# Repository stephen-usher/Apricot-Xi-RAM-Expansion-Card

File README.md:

# Apricot-Xi-RAM-Expansion-Card
ACT Apricot Xi/PC RAM expansion card.

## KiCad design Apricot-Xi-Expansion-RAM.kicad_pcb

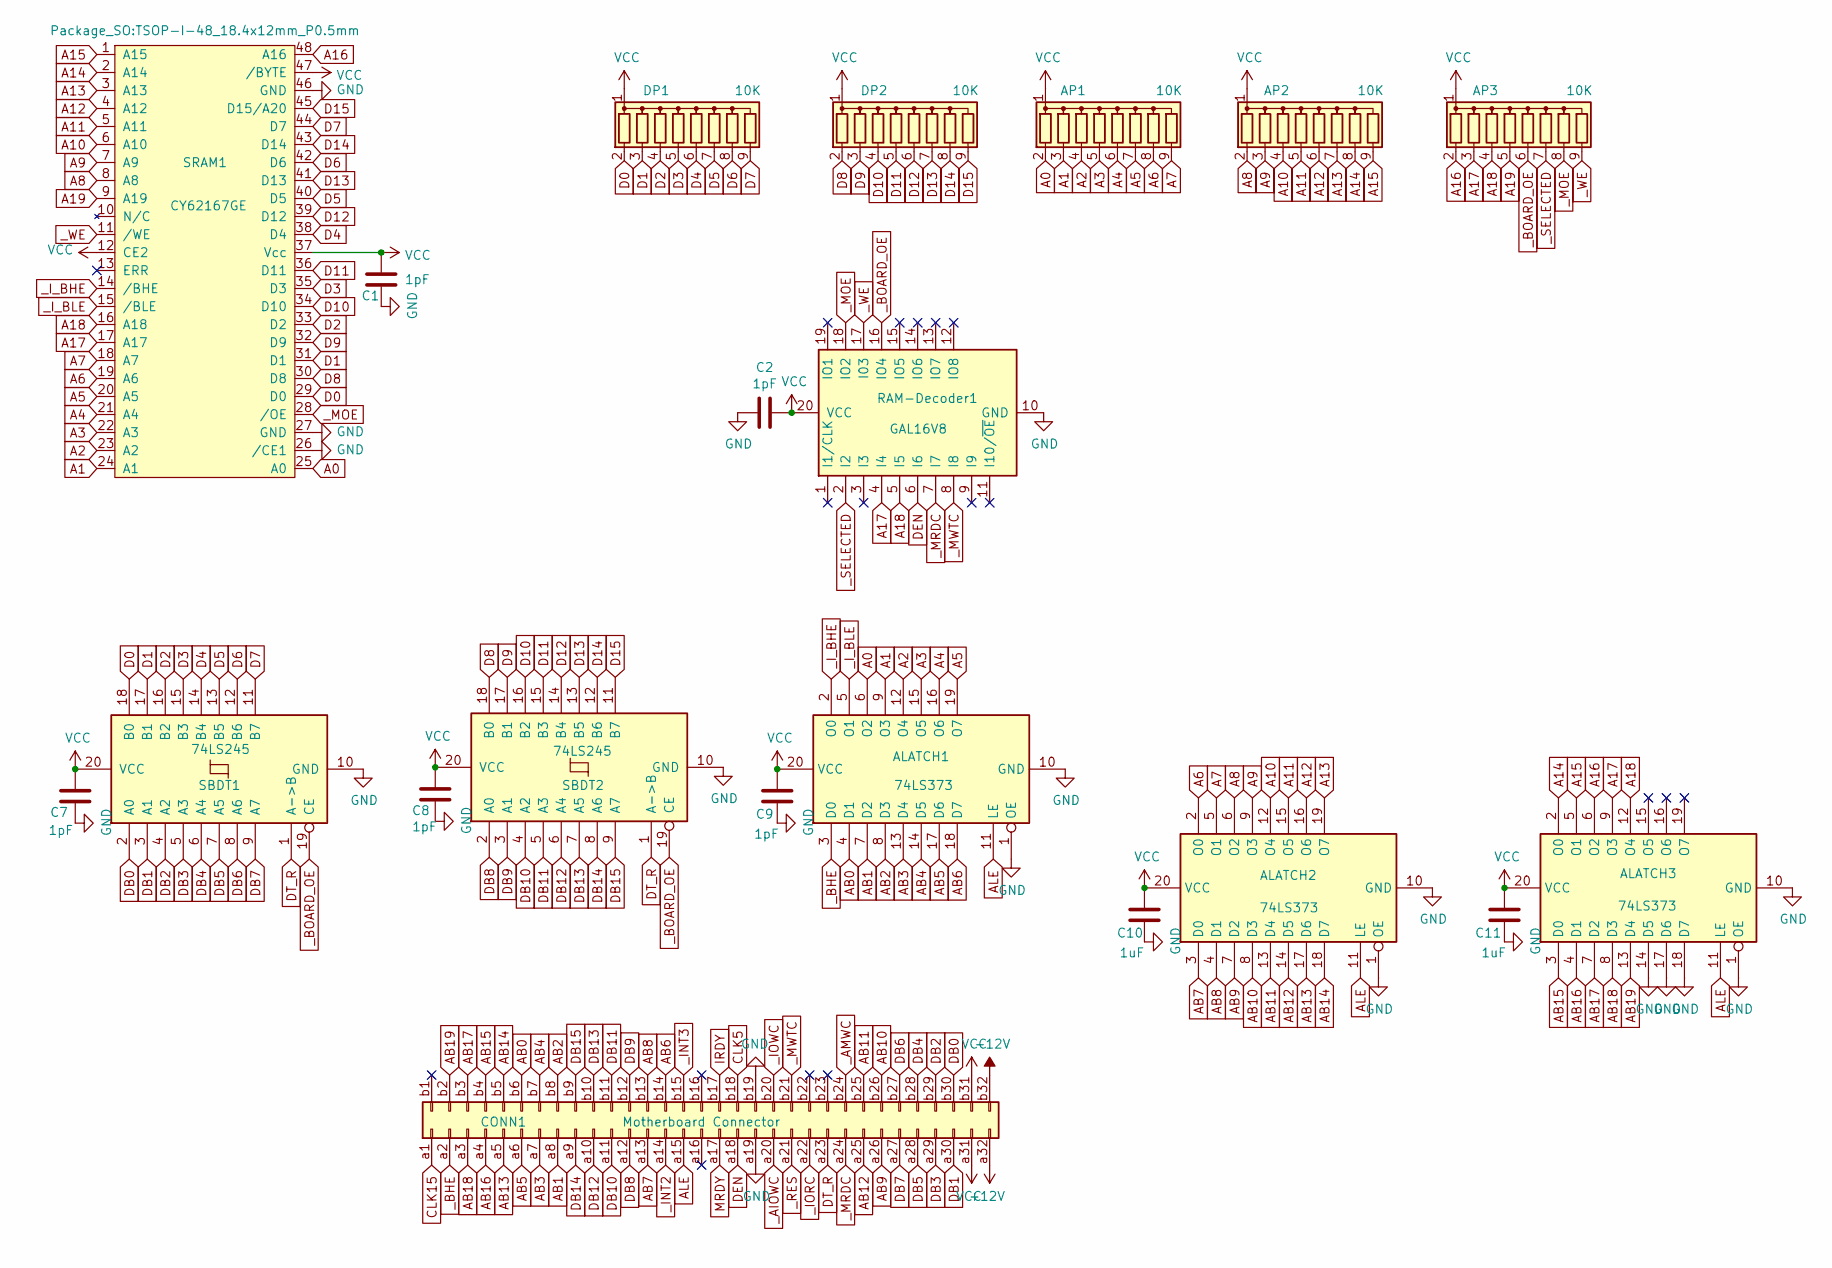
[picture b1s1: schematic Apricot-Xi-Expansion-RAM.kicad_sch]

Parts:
ALATCH1, ALATCH2, ALATCH3: 74LS373; DIP-20_W7.62mm_Socket
AP1, AP2, AP3: 10K; R_Array_SIP9
C1, C2, C7, C8, C9: 1pF; C_0805_2012Metric
C10, C11: 1uF; C_0805_2012Metric
CONN1: Motherboard Connector; DIN41612_B_2x32_Male_Horizontal_THT
DP1, DP2: 10K; R_Array_SIP9
RAM-Decoder1: GAL16V8; DIP-20_W7.62mm_Socket
SBDT1, SBDT2: 74LS245; DIP-20_W7.62mm_Socket
SRAM1: CY62167GE; TSOP-I-48_18.4x12mm_P0.5mm

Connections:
+12V: CONN1.a32
-12V: CONN1.b32
A0: ALATCH1.6 (O2), AP1.2 (R1), SRAM1.25 (A0)
A1: ALATCH1.9 (O3), AP1.3 (R2), SRAM1.24 (A1)
A2: ALATCH1.12 (O4), AP1.4 (R3), SRAM1.23 (A2)
A3: ALATCH1.15 (O5), AP1.5 (R4), SRAM1.22 (A3)
A4: ALATCH1.16 (O6), AP1.6 (R5), SRAM1.21 (A4)
A5: ALATCH1.19 (O7), AP1.7 (R6), SRAM1.20 (A5)
A6: ALATCH2.2 (O0), AP1.8 (R7), SRAM1.19 (A6)
A7: ALATCH2.5 (O1), AP1.9 (R8), SRAM1.18 (A7)
A8: ALATCH2.6 (O2), AP2.2 (R1), SRAM1.8 (A8)
A9: ALATCH2.9 (O3), AP2.3 (R2), SRAM1.7 (A9)
A10: ALATCH2.12 (O4), AP2.4 (R3), SRAM1.6 (A10)
A11: ALATCH2.15 (O5), AP2.5 (R4), SRAM1.5 (A11)
A12: ALATCH2.16 (O6), AP2.6 (R5), SRAM1.4 (A12)
A13: ALATCH2.19 (O7), AP2.7 (R6), SRAM1.3 (A13)
A14: ALATCH3.2 (O0), AP2.8 (R7), SRAM1.2 (A14)
A15: ALATCH3.5 (O1), AP2.9 (R8), SRAM1.1 (A15)
A16: ALATCH3.6 (O2), AP3.2 (R1), SRAM1.48 (A16)
A17: ALATCH3.9 (O3), AP3.3 (R2), RAM-Decoder1.4 (I4), SRAM1.17 (A17)
A18: ALATCH3.12 (O4), AP3.4 (R3), RAM-Decoder1.5 (I5), SRAM1.16 (A18)
A19: AP3.5 (R4), SRAM1.9 (A19)
AB0: ALATCH1.4 (D1), CONN1.b6
AB1: ALATCH1.7 (D2), CONN1.a8
AB2: ALATCH1.8 (D3), CONN1.b8
AB3: ALATCH1.13 (D4), CONN1.a7
AB4: ALATCH1.14 (D5), CONN1.b7
AB5: ALATCH1.17 (D6), CONN1.a6
AB6: ALATCH1.18 (D7), CONN1.b14
AB7: ALATCH2.3 (D0), CONN1.a13
AB8: ALATCH2.4 (D1), CONN1.b13
AB9: ALATCH2.7 (D2), CONN1.a26
AB10: ALATCH2.8 (D3), CONN1.b26
AB11: ALATCH2.13 (D4), CONN1.b25
AB12: ALATCH2.14 (D5), CONN1.a25
AB13: ALATCH2.17 (D6), CONN1.a5
AB14: ALATCH2.18 (D7), CONN1.b5
AB15: ALATCH3.3 (D0), CONN1.b4
AB16: ALATCH3.4 (D1), CONN1.a4
AB17: ALATCH3.7 (D2), CONN1.b3
AB18: ALATCH3.8 (D3), CONN1.a3
AB19: ALATCH3.13 (D4), CONN1.b2
ALE: ALATCH1.11 (LE), ALATCH2.11 (LE), ALATCH3.11 (LE), CONN1.a15
CLK5: CONN1.b18
CLK15: CONN1.a1
D0: DP1.2 (R1), SBDT1.18 (B0), SRAM1.29 (D0)
D1: DP1.3 (R2), SBDT1.17 (B1), SRAM1.31 (D1)
D2: DP1.4 (R3), SBDT1.16 (B2), SRAM1.33 (D2)
D3: DP1.5 (R4), SBDT1.15 (B3), SRAM1.35 (D3)
D4: DP1.6 (R5), SBDT1.14 (B4), SRAM1.38 (D4)
D5: DP1.7 (R6), SBDT1.13 (B5), SRAM1.40 (D5)
D6: DP1.8 (R7), SBDT1.12 (B6), SRAM1.42 (D6)
D7: DP1.9 (R8), SBDT1.11 (B7), SRAM1.44 (D7)
D8: DP2.2 (R1), SBDT2.18 (B0), SRAM1.30 (D8)
D9: DP2.3 (R2), SBDT2.17 (B1), SRAM1.32 (D9)
D10: DP2.4 (R3), SBDT2.16 (B2), SRAM1.34 (D10)
D11: DP2.5 (R4), SBDT2.15 (B3), SRAM1.36 (D11)
D12: DP2.6 (R5), SBDT2.14 (B4), SRAM1.39 (D12)
D13: DP2.7 (R6), SBDT2.13 (B5), SRAM1.41 (D13)
D14: DP2.8 (R7), SBDT2.12 (B6), SRAM1.43 (D14)
D15: DP2.9 (R8), SBDT2.11 (B7), SRAM1.45 (D15/A20)
DB0: CONN1.b30, SBDT1.2 (A0)
DB1: CONN1.a30, SBDT1.3 (A1)
DB2: CONN1.b29, SBDT1.4 (A2)
DB3: CONN1.a29, SBDT1.5 (A3)
DB4: CONN1.b28, SBDT1.6 (A4)
DB5: CONN1.a28, SBDT1.7 (A5)
DB6: CONN1.b27, SBDT1.8 (A6)
DB7: CONN1.a27, SBDT1.9 (A7)
DB8: CONN1.a12, SBDT2.2 (A0)
DB9: CONN1.b12, SBDT2.3 (A1)
DB10: CONN1.a11, SBDT2.4 (A2)
DB11: CONN1.b11, SBDT2.5 (A3)
DB12: CONN1.a10, SBDT2.6 (A4)
DB13: CONN1.b10, SBDT2.7 (A5)
DB14: CONN1.a9, SBDT2.8 (A6)
DB15: CONN1.b9, SBDT2.9 (A7)
DEN: CONN1.a18, RAM-Decoder1.6 (I6)
DT_R: CONN1.a23, SBDT1.1 (A->B), SBDT2.1 (A->B)
GND: ALATCH1.1 (OE), ALATCH1.10 (GND), ALATCH2.1 (OE), ALATCH2.10 (GND), ALATCH3.1 (OE), ALATCH3.10 (GND), ALATCH3.14 (D5), ALATCH3.17 (D6), ALATCH3.18 (D7), C1.2, C2.2, C7.2, C8.2, C9.2, C10.2, C11.2, CONN1.a19, CONN1.b19, RAM-Decoder1.10 (GND), SBDT1.10 (GND), SBDT2.10 (GND), SRAM1.26 (/CE1), SRAM1.27 (GND), SRAM1.46 (GND)
IRDY: CONN1.b17
MRDY: CONN1.a17
VCC: ALATCH1.20 (VCC), ALATCH2.20 (VCC), ALATCH3.20 (VCC), AP1.1 (common), AP2.1 (common), AP3.1 (common), C1.1, C2.1, C7.1, C8.1, C9.1, C10.1, C11.1, CONN1.a31, CONN1.b31, DP1.1 (common), DP2.1 (common), RAM-Decoder1.20 (VCC), SBDT1.20 (VCC), SBDT2.20 (VCC), SRAM1.12 (CE2), SRAM1.37 (Vcc), SRAM1.47 (/BYTE)
_AIOWC: CONN1.a20
_AMWC: CONN1.b24
_BHE: ALATCH1.3 (D0), CONN1.a2
_BOARD_OE: AP3.6 (R5), RAM-Decoder1.16 (IO4), SBDT1.19 (CE), SBDT2.19 (CE)
_INT2: CONN1.a14
_INT3: CONN1.b15
_IORC: CONN1.a22
_IOWC: CONN1.b20
_I_BHE: ALATCH1.2 (O0), SRAM1.14 (/BHE)
_I_BLE: ALATCH1.5 (O1), SRAM1.15 (/BLE)
_MOE: AP3.8 (R7), RAM-Decoder1.18 (IO2), SRAM1.28 (/OE)
_MRDC: CONN1.a24, RAM-Decoder1.7 (I7)
_MWTC: CONN1.b21, RAM-Decoder1.8 (I8)
_RES: CONN1.a21
_SELECTED: AP3.7 (R6), RAM-Decoder1.2 (I2)
_WE: AP3.9 (R8), RAM-Decoder1.17 (I03), SRAM1.11 (/WE)

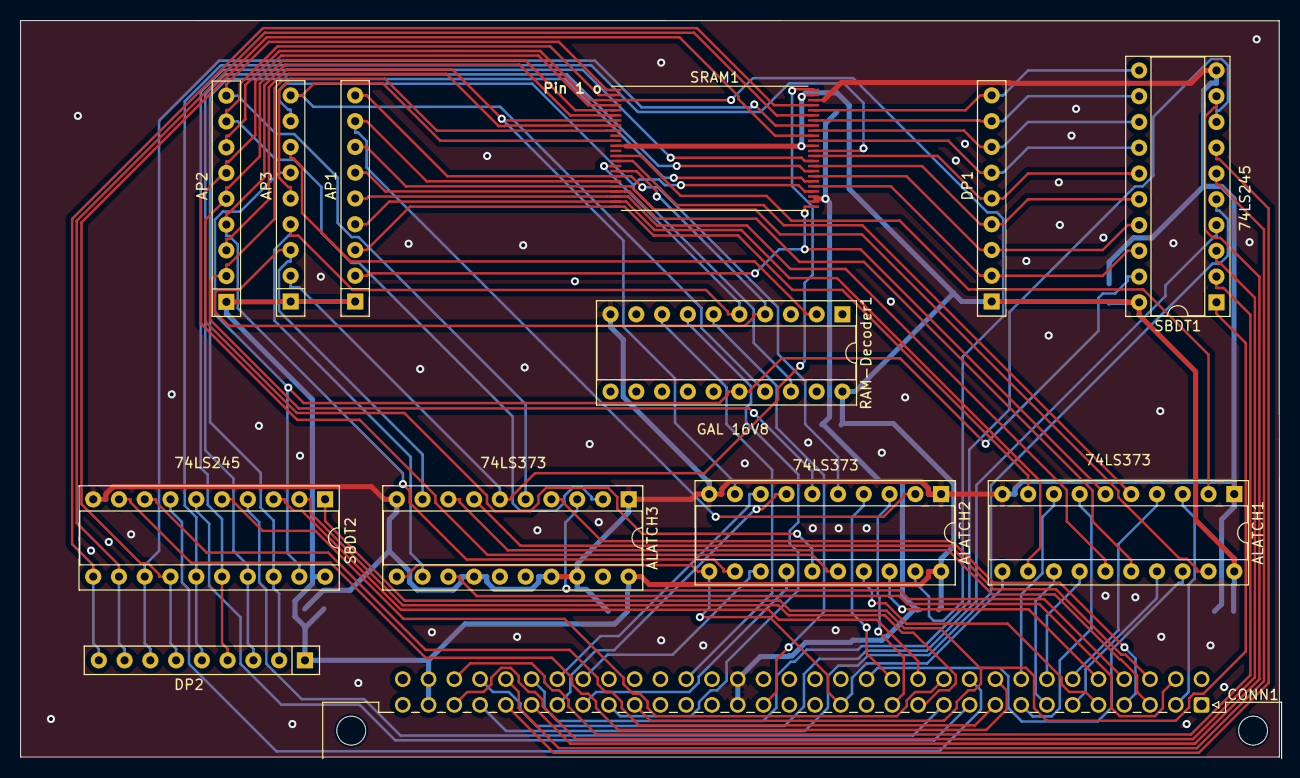
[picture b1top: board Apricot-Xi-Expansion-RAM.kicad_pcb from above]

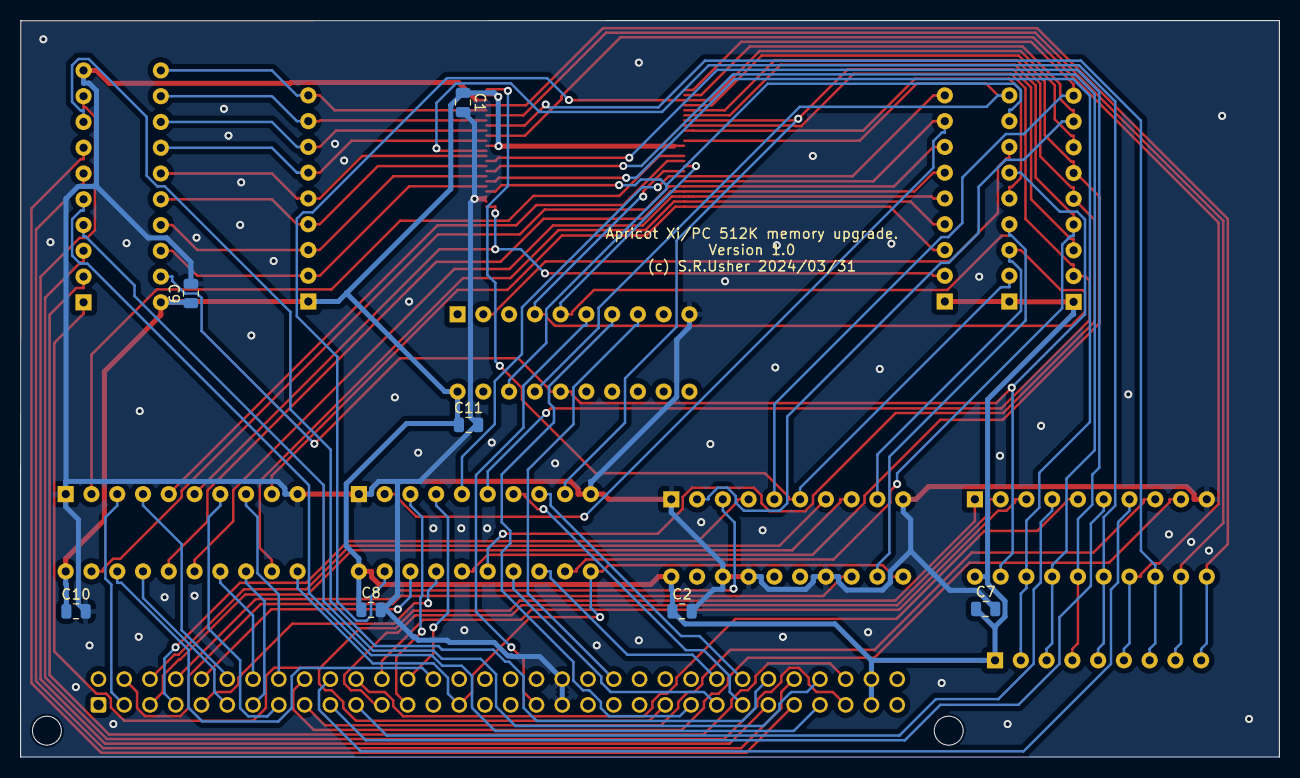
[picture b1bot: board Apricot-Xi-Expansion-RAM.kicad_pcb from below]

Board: 2 copper layers, 124.1 x 72.6 mm, 20 parts (7 on the bottom side), 86 nets.

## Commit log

2026-02-25 Files uploaded
